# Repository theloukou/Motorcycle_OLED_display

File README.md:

# Motorcycle information display
ESP32-based Motorcycle Information Display

This is an ESP32 based system, intented for older motorcycles. It is an expansion of the AVR implementation found in the main_avr branch.
It utilizes a small 128x32 OLED diplay module to display motor and ambient temperatures from a set of NTC thermistor/DS18B20, as well as time information through an RTC IC.

New features compared to the Arduino/AVR version are:
* Syncing RTC time via onboard web server
* Uploading new firmware via Wifi, without need to remove system/connect to PC
* Custom PCB to minimize system footprint. Choice between pin-compatible DS1307/PCF8523

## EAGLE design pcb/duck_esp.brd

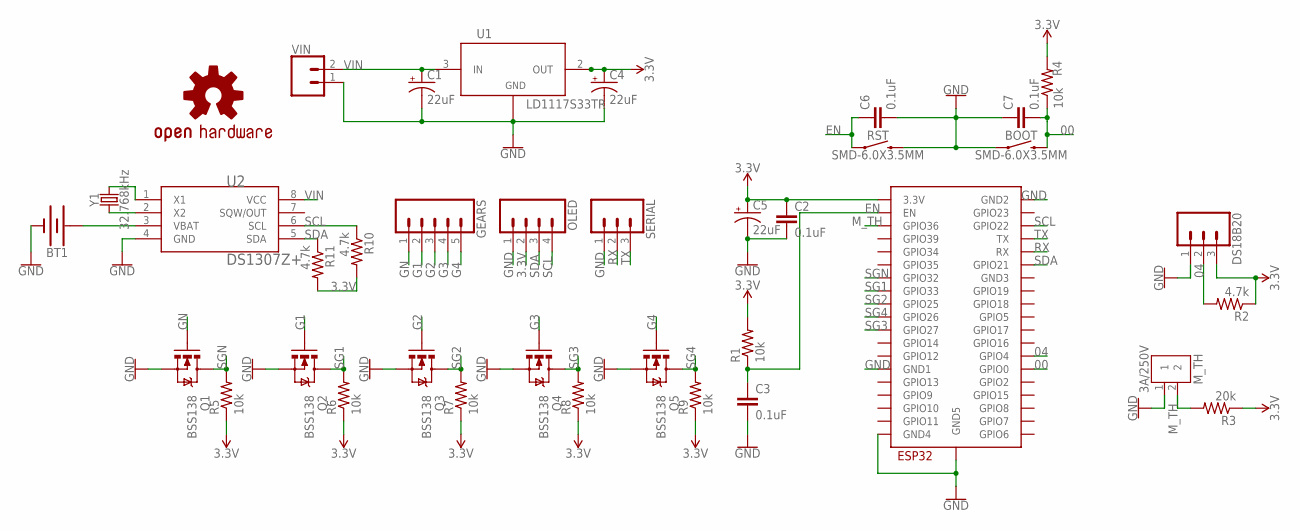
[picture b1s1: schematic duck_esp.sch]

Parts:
BOOT: SMD-6.0X3.5MM; TACTILE_SWITCH_SMD_6.0X3.5MM
BT1: BATTERY-12MM_SMD; BATTCON_12MM
C1, C4, C5: 22uF; E2-5
C2, C3, C6, C7: 0.1uF; 0805
DS18B20: CONN_03; 1X03
GEARS: CONN_05; 1X05
LOGO1: OSHW-LOGOL-COPPER; OSHW-LOGO-L_COPPER
M_TH: 3A/250V; B2B-XH-A
OLED: CONN_04; 1X04
Q1, Q2, Q3, Q4, Q5: BSS138; SOT23
R1, R4, R5, R6, R7, R8, R9: 10k; R0805
R2, R10, R11: 4.7k; R0805
R3: 20k; R0805
RST: SMD-6.0X3.5MM; TACTILE_SWITCH_SMD_6.0X3.5MM
SERIAL: CONN_03; 1X03
U1: LD1117S33TR; SOT-223
U2: DS1307Z+; SOIC-8N
U$1: ESP32-WROOM
VIN: CONN_02POLAR; MOLEX-1X2
Y1: 32.768kHz; CRYSTAL-SMD-2X6-CYL

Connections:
00: BOOT.2, C7.2, R4.1, U$1.IO0 (GPIO0)
3.3V: C2.1, C4.+, C5.+, DS18B20.3, OLED.2, R1.2, R2.1, R3.1, R4.2, R5.1, R6.1, R7.1, R8.1, R9.1, R10.2, R11.2, U1.2 (OUT), U1.4, U$1.3V3 (3.3V)
04: DS18B20.2, R2.2, U$1.IO4 (GPIO4)
EN: C3.1, C6.1, R1.1, RST.1, U$1.EN
G1: GEARS.2, Q2.1 (G)
G2: GEARS.3, Q3.1 (G)
G3: GEARS.4, Q4.1 (G)
G4: GEARS.5, Q5.1 (G)
GN: GEARS.1, Q1.1 (G)
GND: BOOT.1, BT1.GND (-), C1.-, C2.2, C3.2, C4.-, C5.-, C6.2, C7.1, DS18B20.1, M_TH.1, OLED.1, Q1.2 (S), Q2.2 (S), Q3.2 (S), Q4.2 (S), Q5.2 (S), RST.2, SERIAL.1, U1.1 (ADJ/GND), U2.4 (GND), U$1.GND1, U$1.GND2, U$1.GND4, U$1.GND5, VIN.1
M_TH: M_TH.2, R3.2, U$1.SENSOR_VP (GPIO36)
RX: SERIAL.2, U$1.RX
SCL: OLED.4, R10.1, U2.6 (SCL), U$1.IO22 (GPIO22)
SDA: OLED.3, R11.1, U2.5 (SDA), U$1.IO21 (GPIO21)
SG1: Q2.3 (D), R6.2, U$1.IO33 (GPIO33)
SG2: Q3.3 (D), R7.2, U$1.IO25 (GPIO25)
SG3: Q4.3 (D), R8.2, U$1.IO27 (GPIO27)
SG4: Q5.3 (D), R9.2, U$1.IO26 (GPIO26)
SGN: Q1.3 (D), R5.2, U$1.IO32 (GPIO32)
TX: SERIAL.3, U$1.TX
VBAT: BT1.PWR@1 (+), U2.3 (VBAT)
VIN: C1.+, U1.3 (IN), U2.8 (VCC), VIN.2
X1: U2.1 (X1), Y1.X2 (2)
X2: U2.2 (X2), Y1.X1 (1)

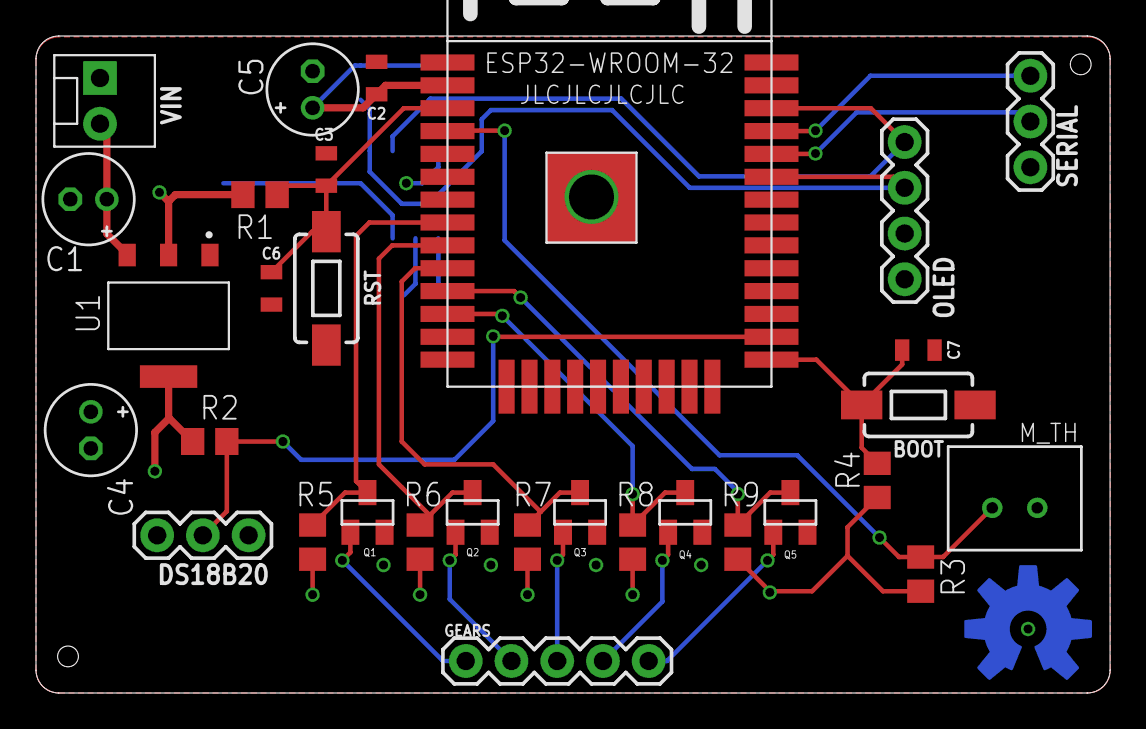
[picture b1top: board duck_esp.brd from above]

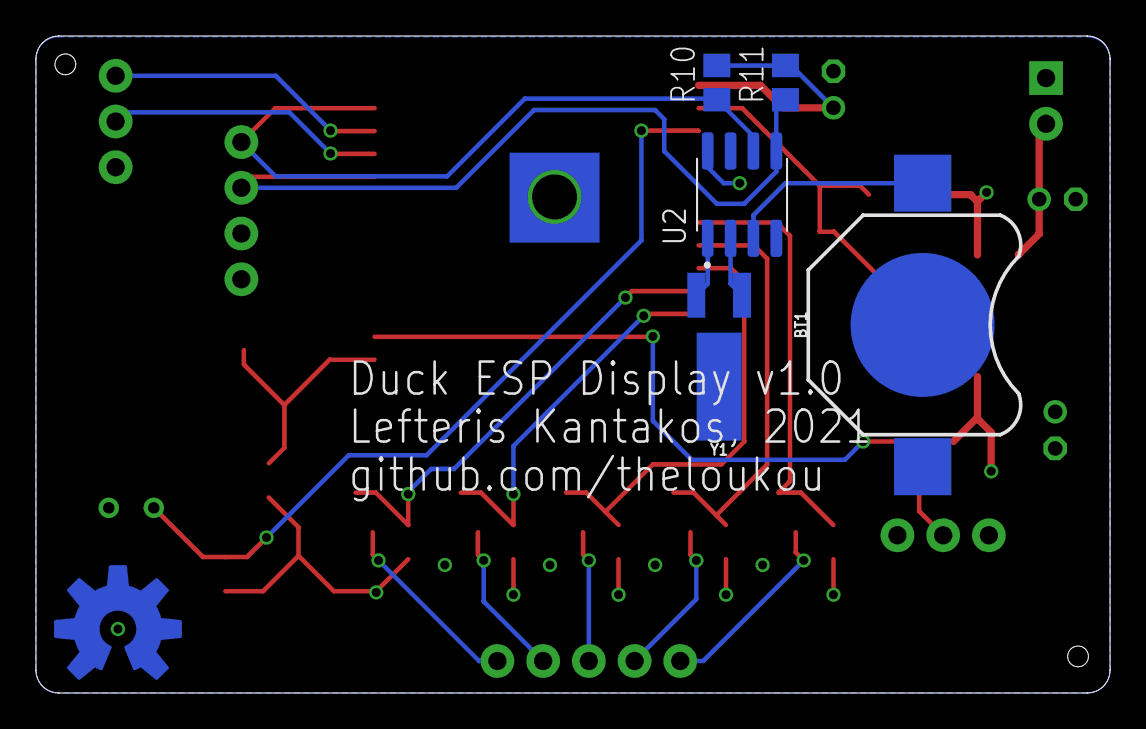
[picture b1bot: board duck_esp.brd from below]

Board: 4 copper layers, 59.7 x 36.5 mm, 37 parts (6 on the bottom side), 24 nets.

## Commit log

2021-10-14 minor pcb layout changes

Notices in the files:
parts and their libraries:
SparkFun-Capacitors: Licensing: Creative Commons ShareAlike 4.0 International - https://creativecommons.org/licenses/by-sa/4.0
